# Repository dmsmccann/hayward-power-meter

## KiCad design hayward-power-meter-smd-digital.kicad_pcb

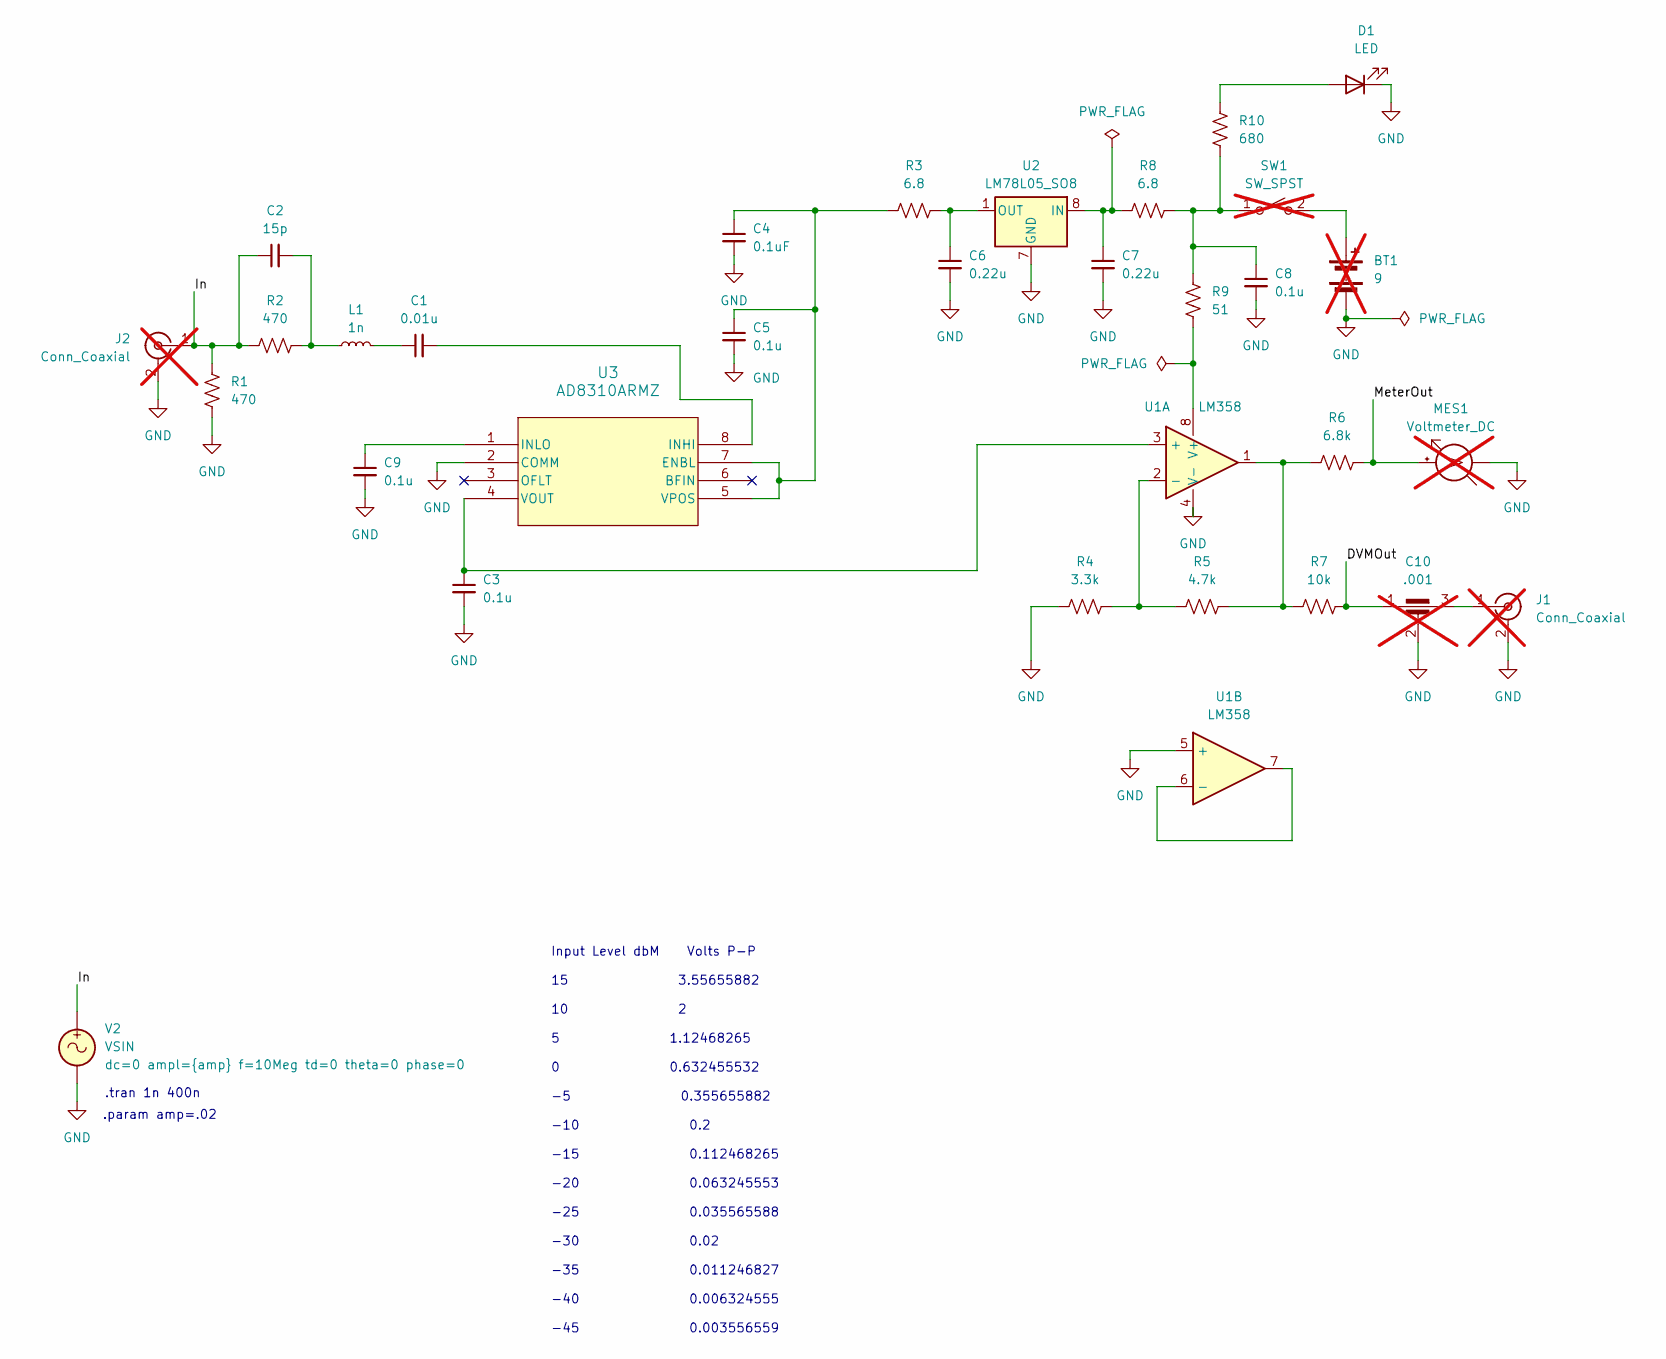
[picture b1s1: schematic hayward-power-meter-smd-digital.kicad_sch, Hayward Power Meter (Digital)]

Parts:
BT1: 9; SolderWire-0.5sqmm_1x02_P4.8mm_D0.9mm_OD2.3mm; not fitted
C1: 0.01u; C_0805_2012Metric
C2: 15p; C_0805_2012Metric
C3, C5, C8, C9: 0.1u; C_0805_2012Metric
C4: 0.1uF; C_0805_2012Metric
C6, C7: 0.22u; C_0805_2012Metric
C10: .001; SolderWire-0.5sqmm_1x02_P4.8mm_D0.9mm_OD2.3mm; not fitted
D1: LED; SolderWire-0.5sqmm_1x02_P4.8mm_D0.9mm_OD2.3mm
J1, J2: Conn_Coaxial; SolderWire-0.5sqmm_1x02_P4.8mm_D0.9mm_OD2.3mm; not fitted
L1: 1n; L_0805_2012Metric
MES1: Voltmeter_DC; SolderWire-0.5sqmm_1x02_P4.8mm_D0.9mm_OD2.3mm; not fitted
R1, R2: 470; R_0805_2012Metric
R3, R8: 6.8; R_0805_2012Metric
R4: 3.3k; R_0805_2012Metric
R5: 4.7k; R_0805_2012Metric
R6: 6.8k; R_0805_2012Metric
R7: 10k; R_0805_2012Metric
R9: 51; R_0805_2012Metric
R10: 680; R_0805_2012Metric
SW1: SW_SPST; SolderWire-0.5sqmm_1x02_P4.8mm_D0.9mm_OD2.3mm; not fitted
U1: LM358; SOIC-8_3.9x4.9mm_P1.27mm
U2: LM78L05_SO8; SOIC-8_3.9x4.9mm_P1.27mm
U3: AD8310ARMZ; RM_8_ADI
V2: VSIN

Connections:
/DVMOut: C10.1, R7.2
/In: C2.1, J2.1 (In), R1.2, R2.1, V2.1
/MeterOut: MES1.2 (+), R6.2
GND: BT1.2 (-), C3.2, C4.2, C5.2, C6.2, C7.2, C8.2, C9.2, C10.2, D1.1 (K), J1.2 (Ext), J2.2 (Ext), MES1.1 (-), R1.1, R4.1, U1.4 (V-), U1.5 (+), U2.2 (GND), U2.3 (GND), U2.6 (GND), U2.7 (GND), U3.2 (COMM), V2.2
unnamed: BT1.1 (+), SW1.2 (B)
unnamed: C1.1, L1.2
unnamed: C2.2, L1.1, R2.2
unnamed: D1.2 (A), R10.1
unnamed: C10.3, J1.1 (In)
unnamed: R5.2, R6.1, R7.1, U1.1
unnamed: C8.1, R8.2, R9.2, R10.2, SW1.1 (A)
unnamed: C3.1, U1.3 (+), U3.4 (VOUT)
unnamed: R4.2, R5.1, U1.2 (-)
unnamed: U1.6 (-), U1.7
unnamed: R9.1, U1.8 (V+)
unnamed: C7.1, R8.1, U2.8 (IN)
unnamed: C6.1, R3.2, U2.1 (OUT)
unnamed: C4.1, C5.1, R3.1, U3.5 (VPOS), U3.7 (ENBL)
unnamed: C1.2, U3.8 (INHI)
unnamed: C9.1, U3.1 (INLO)

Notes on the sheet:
.param amp=.02
Input Level dbM Volts P-P 15 3.55655882 10 2 5 1.12468265 0 0.632455532 -5 0.355655882 -10 0.2 -15 0.112468265 -20 0.063245553 -25 0.035565588 -30 0.02 -35 0.011246827 -40 0.006324555 -45 0.003556559
.tran 1n 400n

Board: 2 copper layers, 30 parts (0 on the bottom side), 19 nets, no tracks yet.

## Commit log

2024-08-04 original meter
    Original Hayward analog design
2024-08-04 New LtSpice Sim with AD8541
